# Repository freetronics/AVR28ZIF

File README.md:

Freetronics 28-Pin AVR ZIF Breakout
===================================
Copyright 2016 Freetronics Pty Ltd  
Freetronics site:  www.freetronics.com  
Freetronics email: info@freetronics.com  

Breakout for a 28-pin ZIF (Zero Insertion Force) for AVR microcontrollers,
with headers for ICSP and USB-to-Serial connections. Includes an onboard
crystal and LED on Arduino pin D13.

Features:

 * 28-pin ZIF socket
 * Header for FTDI-compatible USB-to-Serial cable
 * Header for 6-pin ICSP cable
 * Power source selection jumper
 * Power LED
 * LED on Arduino pin D13
 * Crystal and capacitors
 * Reset button

More information is available at:

  http://www.freetronics.com/avr28zif

INSTALLATION
------------
The design is saved as an EAGLE project. EAGLE PCB design software is
available from www.cadsoftusa.com free for non-commercial use. To use
this project download it and place the directory containing these files
into the "eagle" directory on your computer.

DISTRIBUTION
------------
The specific terms of distribution of this project are governed by the
license referenced below.

LICENSE
-------
Licensed under the TAPR Open Hardware License (www.tapr.org/OHL).
The "license" folder within this repository also contains a copy of
this license in plain text format.

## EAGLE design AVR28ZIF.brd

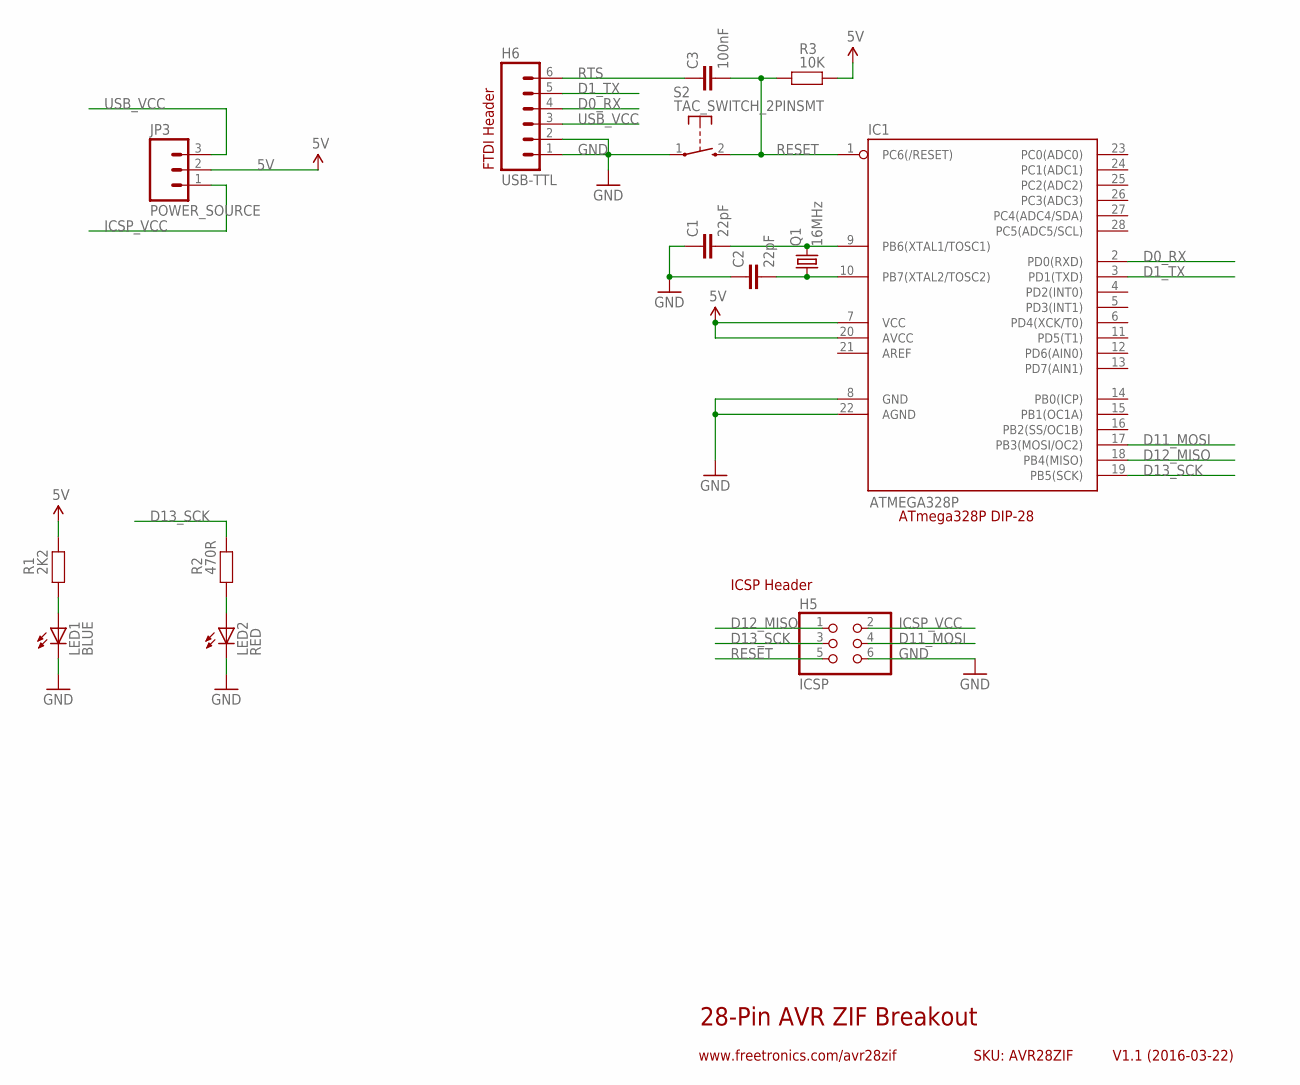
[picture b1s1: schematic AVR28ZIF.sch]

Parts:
C1, C2: 22pF; 0603
C3: 100nF; 0603
H5: ICSP; 2X03
H6: USB-TTL; 1X06
IC1: ATMEGA328P; DIL28-3-ZIF
JP3: POWER_SOURCE; 1X03
LED1: BLUE; LED-0603
LED2: RED; LED-0603
Q1: 16MHz; HC49US
R1: 2K2; 0603
R2: 470R; 0603
R3: 10K; 0603
S2: TAC_SWITCH_2PINSMT; TACTILE_SWITCH_SMD_2PIN_TINY

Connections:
5V: IC1.7 (VCC), IC1.20 (AVCC), JP3.2, R1.2, R3.2
D0_RX: H6.4, IC1.2 (PD0(RXD))
D1_TX: H6.5, IC1.3 (PD1(TXD))
D11_MOSI: H5.4, IC1.17 (PB3(MOSI/OC2))
D12_MISO: H5.1, IC1.18 (PB4(MISO))
D13_SCK: H5.3, IC1.19 (PB5(SCK)), R2.2
GND: C1.1, C2.1, H5.6, H6.1, H6.2, IC1.8 (GND), IC1.22 (AGND), LED1.C, LED2.C, S2.1
ICSP_VCC: H5.2, JP3.1
unnamed: C1.2, IC1.9 (PB6(XTAL1/TOSC1)), Q1.2
unnamed: C2.2, IC1.10 (PB7(XTAL2/TOSC2)), Q1.1
unnamed: LED1.A, R1.1
unnamed: LED2.A, R2.1
RESET: C3.2, H5.5, IC1.1 (PC6(/RESET)), R3.1, S2.2 (S)
RTS: C3.1, H6.6
USB_VCC: H6.3, JP3.3

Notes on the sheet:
28-Pin AVR ZIF Breakout
V1.1 (2016-03-22)
SKU: AVR28ZIF
www.freetronics.com/avr28zif
ATmega328P DIP-28
ICSP Header
FTDI Header

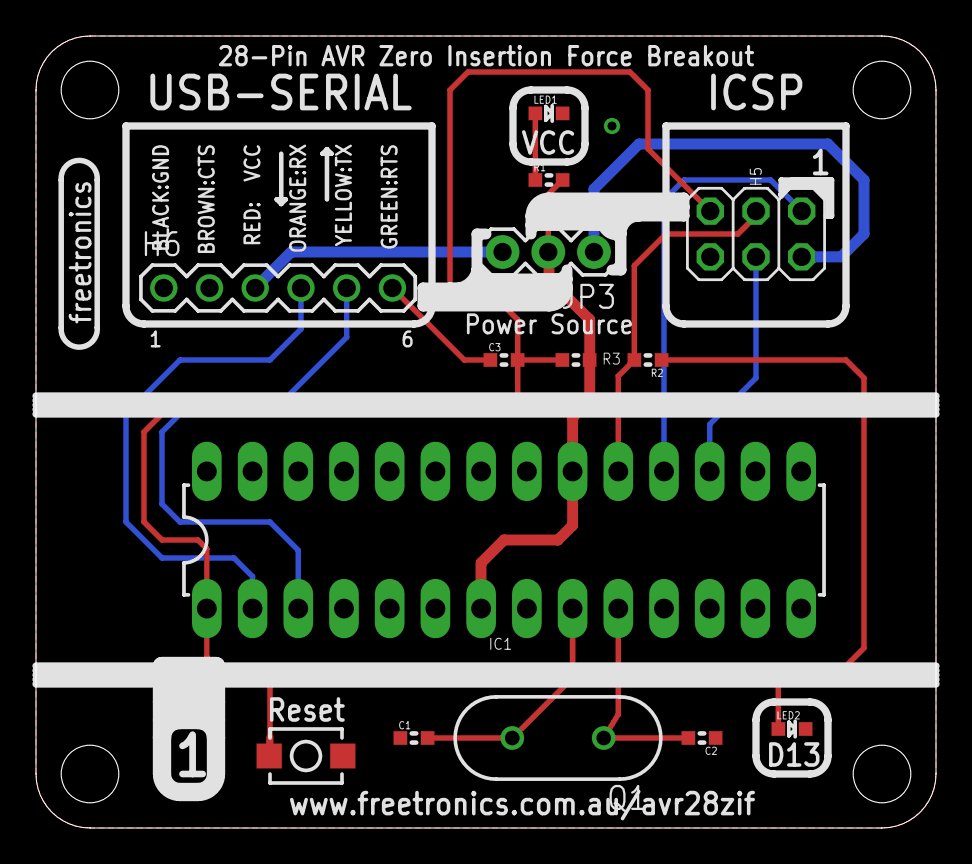
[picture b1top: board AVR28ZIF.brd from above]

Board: 2 copper layers, 50.0 x 44.0 mm, 14 parts (0 on the bottom side), 15 nets.

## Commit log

2016-03-23 Initial import of project for v1.1 release
2018-03-22 Updated part value labels

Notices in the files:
AVR28ZIF.brd:
(C)2016 Freetronics Pty Ltd
parts and their libraries:
freetronics-original: Licensing: CC v3.0 Share-Alike You are welcome to use this library for commercial purposes.
